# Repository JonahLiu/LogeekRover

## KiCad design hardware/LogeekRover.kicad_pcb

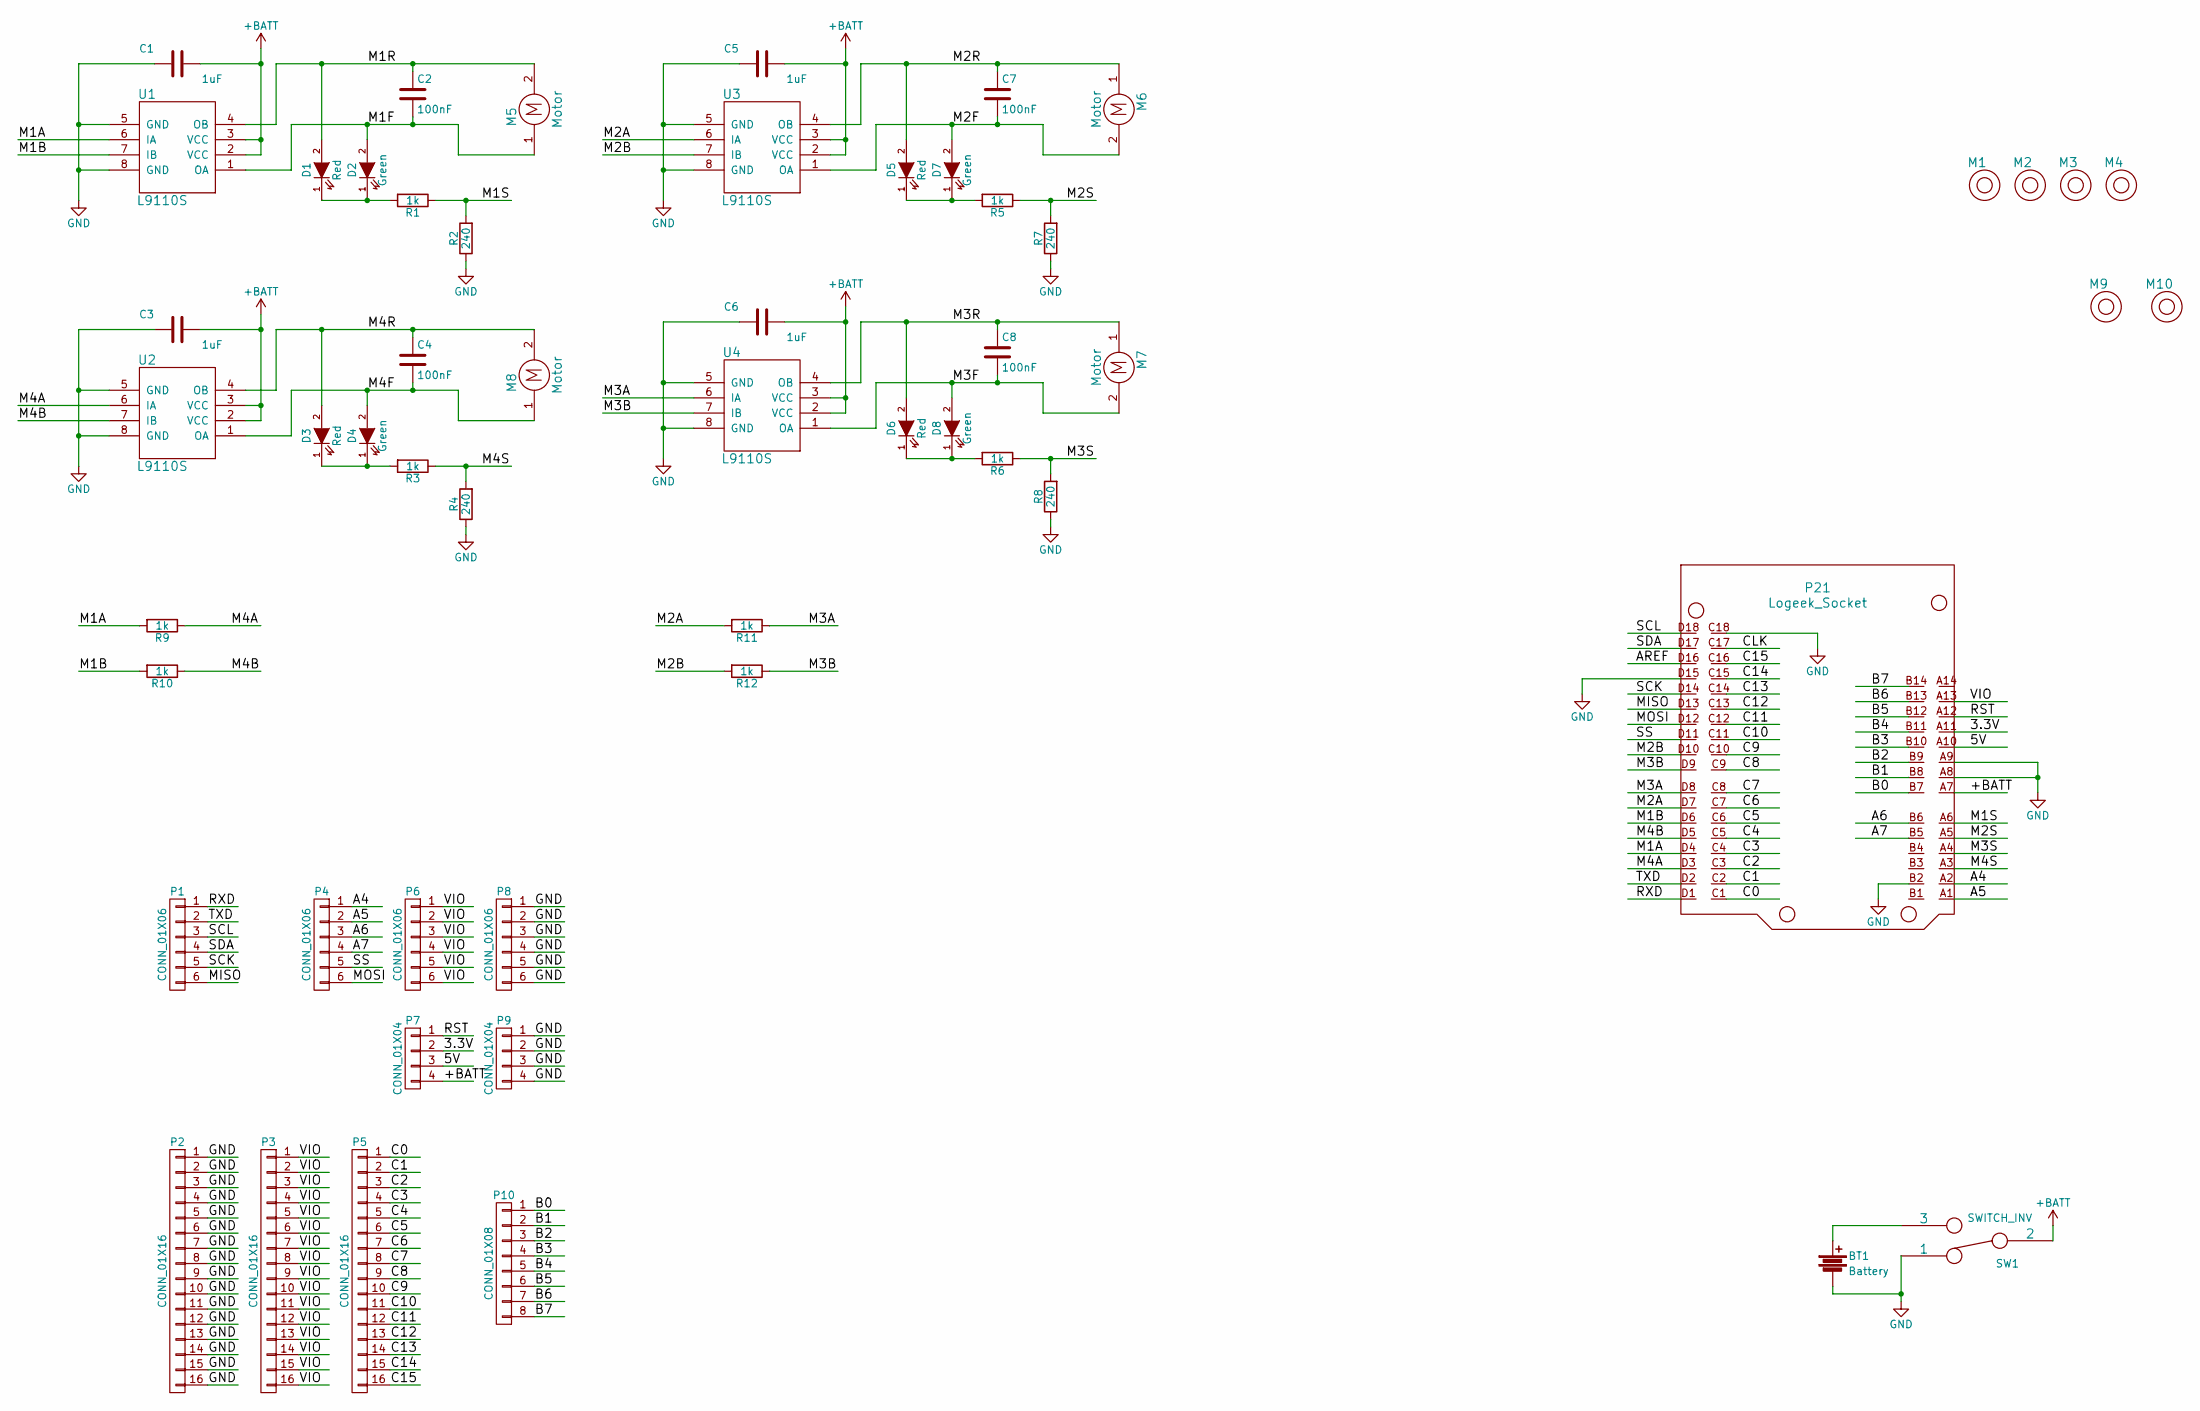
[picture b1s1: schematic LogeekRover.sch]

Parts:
BT1: Battery; Battery_Case_AAAx2
C1, C3, C5, C6: 1uF; C_0603_HandSoldering
C2, C4, C7, C8: 100nF; C_0603_HandSoldering
D1, D3, D5, D6: Red; LED-0603
D2, D4, D7, D8: Green; LED-0603
M1, M2, M3, M4, M9, M10: Mounting_Hole; Mounting_Hole_3mm
M5, M6, M7, M8: Motor; N20_Mount_Rack
P1, P4, P6, P8: CONN_01X06; Socket_Strip_Straight_1x06
P2, P3, P5: CONN_01X16; Socket_Strip_Straight_1x16
P7, P9: CONN_01X04; Socket_Strip_Straight_1x04
P10: CONN_01X08; Socket_Strip_Straight_1x08
P21: Logeek_Socket; Logeek_Socket_SMD
R1, R3, R5, R6, R9, R10, R11, R12: 1k; R_0603_HandSoldering
R2, R4, R7, R8: 240; R_0603_HandSoldering
SW1: SWITCH_INV; SS-12D07
U1, U2, U3, U4: L9110S; SOIC-8-N

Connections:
+BATT: C1.2, C3.2, C5.2, C6.2, P7.4, P21.A7, SW1.2, U1.2 (VCC), U1.3 (VCC), U2.2 (VCC), U2.3 (VCC), U3.2 (VCC), U3.3 (VCC), U4.2 (VCC), U4.3 (VCC)
/3.3V: P7.2, P21.A11
/5V: P7.3, P21.A10
/A4: P4.1, P21.A2
/A5: P4.2, P21.A1
/A6: P4.3, P21.B6
/A7: P4.4, P21.B5
/AREF: P21.D16
/B0: P10.1, P21.B7
/B1: P10.2, P21.B8
/B2: P10.3, P21.B9
/B3: P10.4, P21.B10
/B4: P10.5, P21.B11
/B5: P10.6, P21.B12
/B6: P10.7, P21.B13
/B7: P10.8, P21.B14
/C0: P5.1, P21.C1
/C1: P5.2, P21.C2
/C2: P5.3, P21.C3
/C3: P5.4, P21.C4
/C4: P5.5, P21.C5
/C5: P5.6, P21.C6
/C6: P5.7, P21.C7
/C7: P5.8, P21.C8
/C8: P5.9, P21.C9
/C9: P5.10, P21.C10
/C10: P5.11, P21.C11
/C11: P5.12, P21.C12
/C12: P5.13, P21.C13
/C13: P5.14, P21.C14
/C14: P5.15, P21.C15
/C15: P5.16, P21.C16
/CLK: P21.C17
/M1A: P21.D4, R9.2, U1.6 (IA)
/M1B: P21.D6, R10.2, U1.7 (IB)
/M1F: C2.2, D2.2 (A), M5.1, U1.1 (OA)
/M1R: C2.1, D1.2 (A), M5.2, U1.4 (OB)
/M1S: P21.A6, R1.1, R2.2
/M2A: P21.D7, R11.2, U3.6 (IA)
/M2B: P21.D10, R12.2, U3.7 (IB)
/M2F: C7.2, D7.2 (A), M6.2, U3.1 (OA)
/M2R: C7.1, D5.2 (A), M6.1, U3.4 (OB)
/M2S: P21.A5, R5.1, R7.2
/M3A: P21.D8, R11.1, U4.6 (IA)
/M3B: P21.D9, R12.1, U4.7 (IB)
/M3F: C8.2, D8.2 (A), M7.2, U4.1 (OA)
/M3R: C8.1, D6.2 (A), M7.1, U4.4 (OB)
/M3S: P21.A4, R6.1, R8.2
/M4A: P21.D3, R9.1, U2.6 (IA)
/M4B: P21.D5, R10.1, U2.7 (IB)
/M4F: C4.2, D4.2 (A), M8.1, U2.1 (OA)
/M4R: C4.1, D3.2 (A), M8.2, U2.4 (OB)
/M4S: P21.A3, R3.1, R4.2
/MISO: P1.6, P21.D13
/MOSI: P4.6, P21.D12
/RST: P7.1, P21.A12
/RXD: P1.1, P21.D1
/SCK: P1.5, P21.D14
/SCL: P1.3, P21.D18
/SDA: P1.4, P21.D17
/SS: P4.5, P21.D11
/TXD: P1.2, P21.D2
/VIO: P3.1, P3.2, P3.3, P3.4, P3.5, P3.6, P3.7, P3.8, P3.9, P3.10, P3.11, P3.12, P3.13, P3.14, P3.15, P3.16, P6.1, P6.2, P6.3, P6.4, P6.5, P6.6, P21.A13
GND: BT1.2, C1.1, C3.1, C5.1, C6.1, P2.1, P2.2, P2.3, P2.4, P2.5, P2.6, P2.7, P2.8, P2.9, P2.10, P2.11, P2.12, P2.13, P2.14, P2.15, P2.16, P8.1, P8.2, P8.3, P8.4, P8.5, P8.6, P9.1, P9.2, P9.3, P9.4, P21.A8, P21.A9, P21.B2, P21.C18, P21.D15, R2.1, R4.1, R7.1, R8.1, SW1.1, U1.5 (GND), U1.8 (GND), U2.5 (GND), U2.8 (GND), U3.5 (GND), U3.8 (GND), U4.5 (GND), U4.8 (GND)
unnamed: BT1.1, SW1.3
unnamed: D1.1 (K), D2.1 (K), R1.2
unnamed: D3.1 (K), D4.1 (K), R3.2
unnamed: D5.1 (K), D7.1 (K), R5.2
unnamed: D6.1 (K), D8.1 (K), R6.2

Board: 2 copper layers, 55 parts (6 on the bottom side), 67 nets, no tracks yet.

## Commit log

2016-01-25 Import
2016-01-25 Daily backup.
2016-01-27 Nightly Backup.
